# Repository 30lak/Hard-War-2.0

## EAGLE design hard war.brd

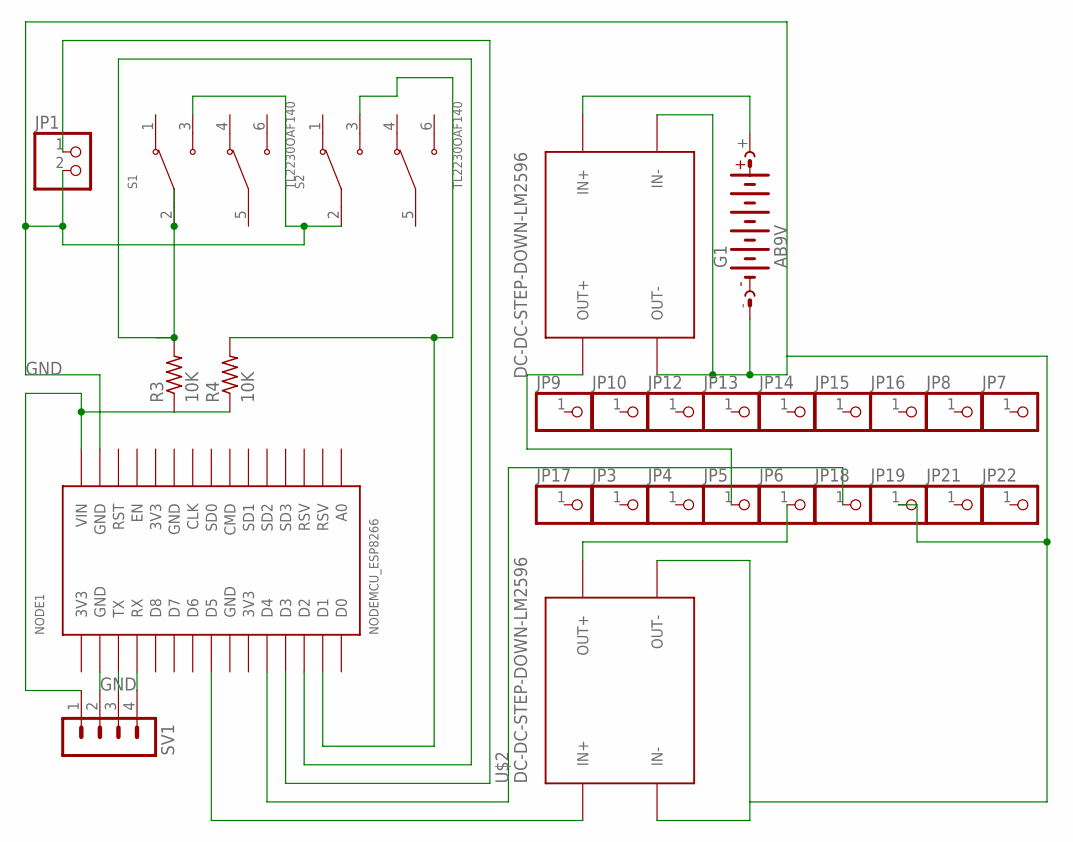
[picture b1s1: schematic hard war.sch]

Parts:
G1: AB9V
JP1: PINHD-1X2; 1X02
JP3, JP4, JP5, JP6, JP7, JP8, JP9, JP10, JP12, JP13, JP14, JP15, JP16, JP17, JP18, JP19, JP21, JP22: PINHD-1X1; 1X01
NODE1: NODEMCU_ESP8266
R3, R4: 10K; 0204/7
S1, S2: TL2230OAF140; SW_TL2230OAF140
SV1: MA04-1
U$1, U$2: DC-DC-STEP-DOWN-LM2596

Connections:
3V3: NODE1.3V3@1 (3V3), NODE1.3V3@2 (3V3), NODE1.3V3@3 (3V3)
GND: G1.-, JP1.2, JP19.1, NODE1.GND@1 (GND), NODE1.GND@2 (GND), NODE1.GND@3 (GND), NODE1.GND@4 (GND), S1.3 (NO1), S2.2 (COM1), SV1.2, U$1.IN-, U$1.OUT-, U$2.IN-, U$2.OUT-
unnamed: NODE1.TX, SV1.3
unnamed: NODE1.RX, SV1.4
unnamed: JP6.1, U$2.OUT+
unnamed: JP5.1, U$1.OUT+
unnamed: NODE1.D2, R3.2, S1.2 (COM1)
unnamed: NODE1.D5, U$2.IN+
unnamed: G1.+, U$1.IN+
unnamed: JP18.1, NODE1.D4
unnamed: NODE1.VIN, R3.1, R4.1, SV1.1
unnamed: JP1.1, NODE1.D3
unnamed: NODE1.D1, R4.2, S2.3 (NO1)

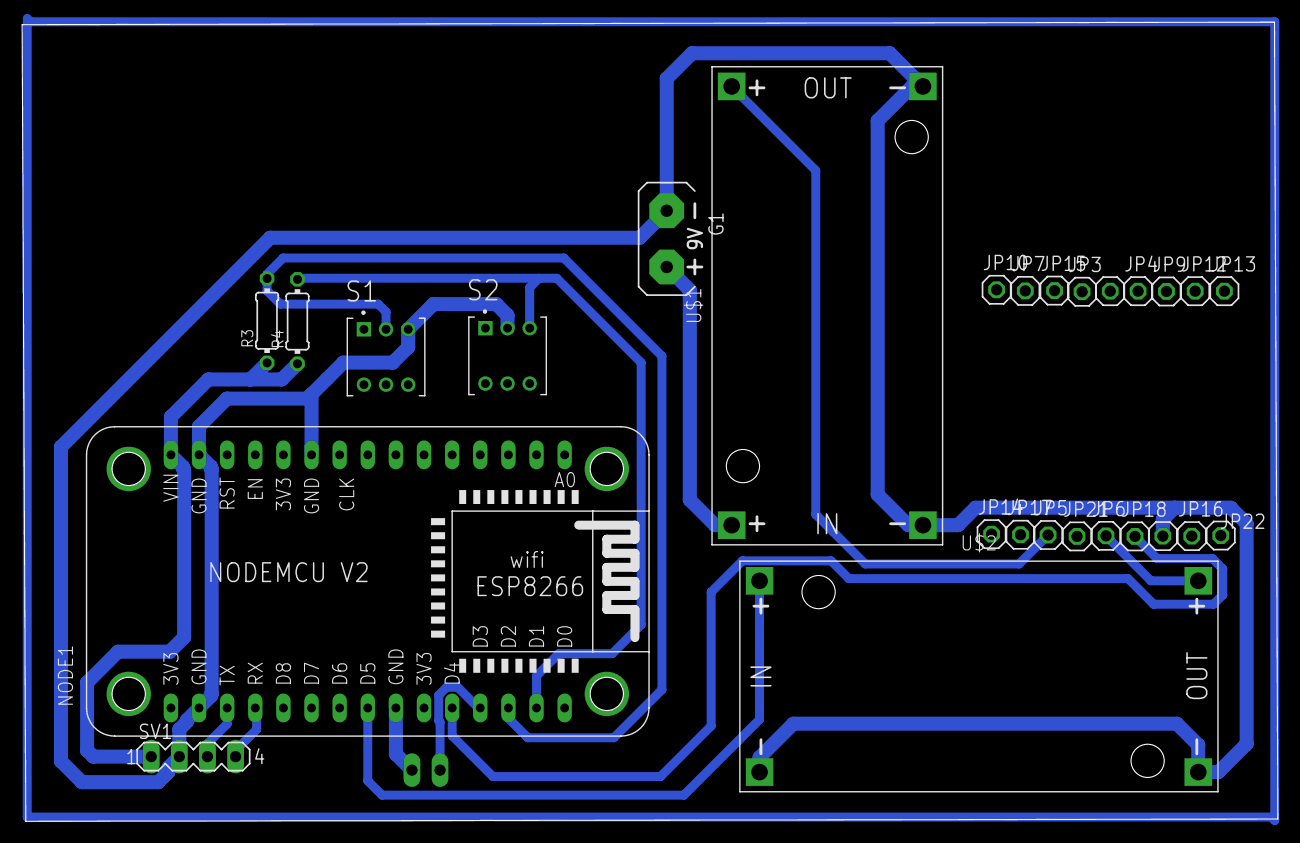
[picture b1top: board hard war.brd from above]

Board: 2 copper layers, 113.4 x 72.2 mm, 28 parts (1 on the bottom side), 13 nets.

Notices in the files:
parts and their libraries:
diy-modules: Released under the Creative Commons Attribution 4.0 International License: http://creativecommons.org/licenses/by/4.0
